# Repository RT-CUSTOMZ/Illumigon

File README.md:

# 💡 Illumigon

Die modularen smarten Leuchtpanels mit Wifi-Konnektivität, die Ihr auf der Campuswoche bauen könnt.

---

## 📦 Features

- [x] Individuell adressierbare LEDs (WS2811)
- [x] WLAN-fähige Steuerung via ESP32
- [x] Konfigurierbare Animationen und Farbpaletten
- [x] Open Source Hardware + Software (WLED)
- [x] Home Assistant Integration
- [x] Modular steckbar
- [x] Keine Kabelsalat

---

## 📁 Dateiübersicht

| Pfad / Datei                | Beschreibung                           |
|----------------------------|-----------------------------------------|
| `Fusion 360/`              | Fusion 360 Archiv und STEP-Modell       |
| `Gerber/`                  | Leiterplattenlayouts im Gerber Format   |
| `KiCad/`                   | Leiterplattenlayouts im KiCad 9 Format  |
| `STLs/`                    | 3D-Modell im STL-Format für den 3D-Druck|
| `SVGs/`                    | Vectorgrafiken zum Laserschneiden und Gravieren      |

## 🧾 Stückliste / Teilebestellung

### 🧠 ESP32 WLED Controller

| Bauteil                 | Referenz                    | Wert                        | Footprint             | Menge | Link  |
|-------------------------|-----------------------------|-----------------------------|-----------------------|-------|-------|
| Keramikkondensator      | C3, C4, C5, C7, C8, C9, C10 | 100n                        | SMD 1206              | 7     |       |
| Keramikkondensator      | C11, C12                    | 22u                         | SMD 1206              | 2     |       |
| Elektrolytkondensator   | C1                          | 470u                        | C_Elec_10x10.2        | 1     |       |
| Keramikkondensator      | C2                          | 1u0                         | SMD 1206              | 1     |       |
| Keramikkondensator      | C6                          | 10u                         | SMD 1206              | 1     |       |
| Dichschichtwiderstand   | R3, R6, R9                  | 100R                        | SMD 0805              | 3     |       |
| Dichschichtwiderstand   | R8, R11, R12                | 10K                         | SMD 1206              | 3     |       |
| Dichschichtwiderstand   | R4, R5                      | 5K1                         | SMD 1206              | 2     |       |
| Dichschichtwiderstand   | R7, R10                     | 4K7                         | SMD 0805              | 2     |       |
| Dichschichtwiderstand   | R1                          | 2K0                         | SMD 0805              | 1     |       |
| Dichschichtwiderstand   | R2                          | 470R                        | SMD 0805              | 1     |       |
| Leistungsinduktor       | L1                          | 4u7                         | 7.3x6.6mm             | 1     |       |
| Leuchtdiode             | D1, D2, D3, D5, D6          | LED                         | SMD 0805              | 5     |       |
| Schottky-Diode          | D4, D7                      | SS34                        | SMA                   | 2     |       |
| 3.3V Spannungswandler   | U1                          | AMS1117-3.3                 | SOT-223-3             | 1     |       |
| 32-bit Mikrocontroller  | U2                          | ESP32-WROOM-32E             |                       | 1     |       |
| 5V Synchr.-Schaltregler | U3                          | AP63205WU                   | TSOT-23-6             | 1     |       |
| 420Mbps Levelshifter    | U4                          | SN74LVC1T45DBV              | SOT-23-6              | 1     |       |
| USB-UART Transceiver    | U5                          | CH340C                      | SOIC-16               | 1     |       |
| Bipolartransistor       | Q2, Q3                      | BC857                       | SOT-23                | 2     |       |
| Bipolartransistor       | Q4, Q5                      | MMBT3904                    | SOT-23                | 2     |       |
| P-Kanal MOSFET          | Q1                          | Q_PMOS_GDS                  | TO-252-2              | 1     |       |
| USB-C-Buchse 16-Pin     | J1                          | USB_C_Receptacle_USB2.0_16P | GCT USB4105           | 1     |       |
| Hohlsteckerbuchse       | J2                          | Barrel_Jack_Switch          |                       | 1     |       |
| Pinheader 2.54 2x3      | J3                          | Conn_02x03_Odd_Even         | 2x03 P2.54mm Vertical | 1     |       |

### 💡 Komponenten je Panel

| Bauteil        | Referenz    | Wert       | Footprint                | Menge | Link |
|----------------|-------------|------------|--------------------------|--------|------|
| Platine        | Ecke        |            |                          | 3      | [GitHub](https://github.com/RT-CUSTOMZ/Illumigon/blob/V4/Gerber/Ecke.zip) |
| Platine        | Seite       |            |                          | 3      | [GitHub](https://github.com/RT-CUSTOMZ/Illumigon/blob/V4/Gerber/Seite.zip) |
| Plexiglas      | Lichtleiter | 4mm klar   | Acrylglas GS             | 1      | [GitHub](https://github.com/RT-CUSTOMZ/Illumigon/blob/e6f71768b751d2ca16ff6e7ad1a84dd5374f7dc3/SVGs/Light_Guide_Panel_fein.svg) |
| Plexiglas      | Diffusor    | 3mm opal   | Acrylglas XT opal 70105  | 1      | [GitHub](https://github.com/RT-CUSTOMZ/Illumigon/blob/e6f71768b751d2ca16ff6e7ad1a84dd5374f7dc3/SVGs/Diffusor.svg) |
| Pinheader 2x3  | J1          | 02x03      | Vertikal                 | 3      | [LCSC](https://www.lcsc.com/product-detail/C492420.html) |
| Pinheader 1x5  | J2, J3      | 01x05      | Horizontal               | 6      | [LCSC](https://www.lcsc.com/product-detail/C492413.html) |
| Platine        | Verbinder   |            |                          | 1      | [GitHub](https://github.com/RT-CUSTOMZ/Illumigon/blob/V4/Gerber/Verbinder.zip) |
| Pinsocket 2x3  | J1, J2      | 02x03      | Vertikal                 | 2      | [LCSC](https://www.lcsc.com/product-detail/C5116527.html) |
| Pinheader 1x2  | J3, J4      | 01x02      | Vertikal                 | 2      | [LCSC](https://www.lcsc.com/product-detail/C492401.html) |
| Jumper 1x2     |             | 01x02      |                          | 1      | [LCSC](https://www.lcsc.com/product-detail/C100114.html) |
| Schraube       |             | PZ 3x10    |                          | 3      | [Schraubenhimmel](https://www.schraubenhimmel.de/schrauben/senkkopf/spanplattenschrauben-kreuzschlitz/65940/spax-wirox-senkkopf-kreuzschlitz-pz-1-3x10-mm-vollgewinde) |
| 3D-Druck       |             | Deckel u.  |                          | 3      | [GitHub](https://github.com/RT-CUSTOMZ/Illumigon/blob/V4/STLs/Deckel_unten%20v49.stl) |
| 3D-Druck       |             | Deckel m.  |                          | 3      | [GitHub](https://github.com/RT-CUSTOMZ/Illumigon/blob/V4/STLs/Deckel_mitte%20v45.stl) |
| 3D-Druck       |             | Verbinder  |                          | 2      | [GitHub](https://github.com/RT-CUSTOMZ/Illumigon/blob/V4/STLs/Verbinder%20v9.stl) |

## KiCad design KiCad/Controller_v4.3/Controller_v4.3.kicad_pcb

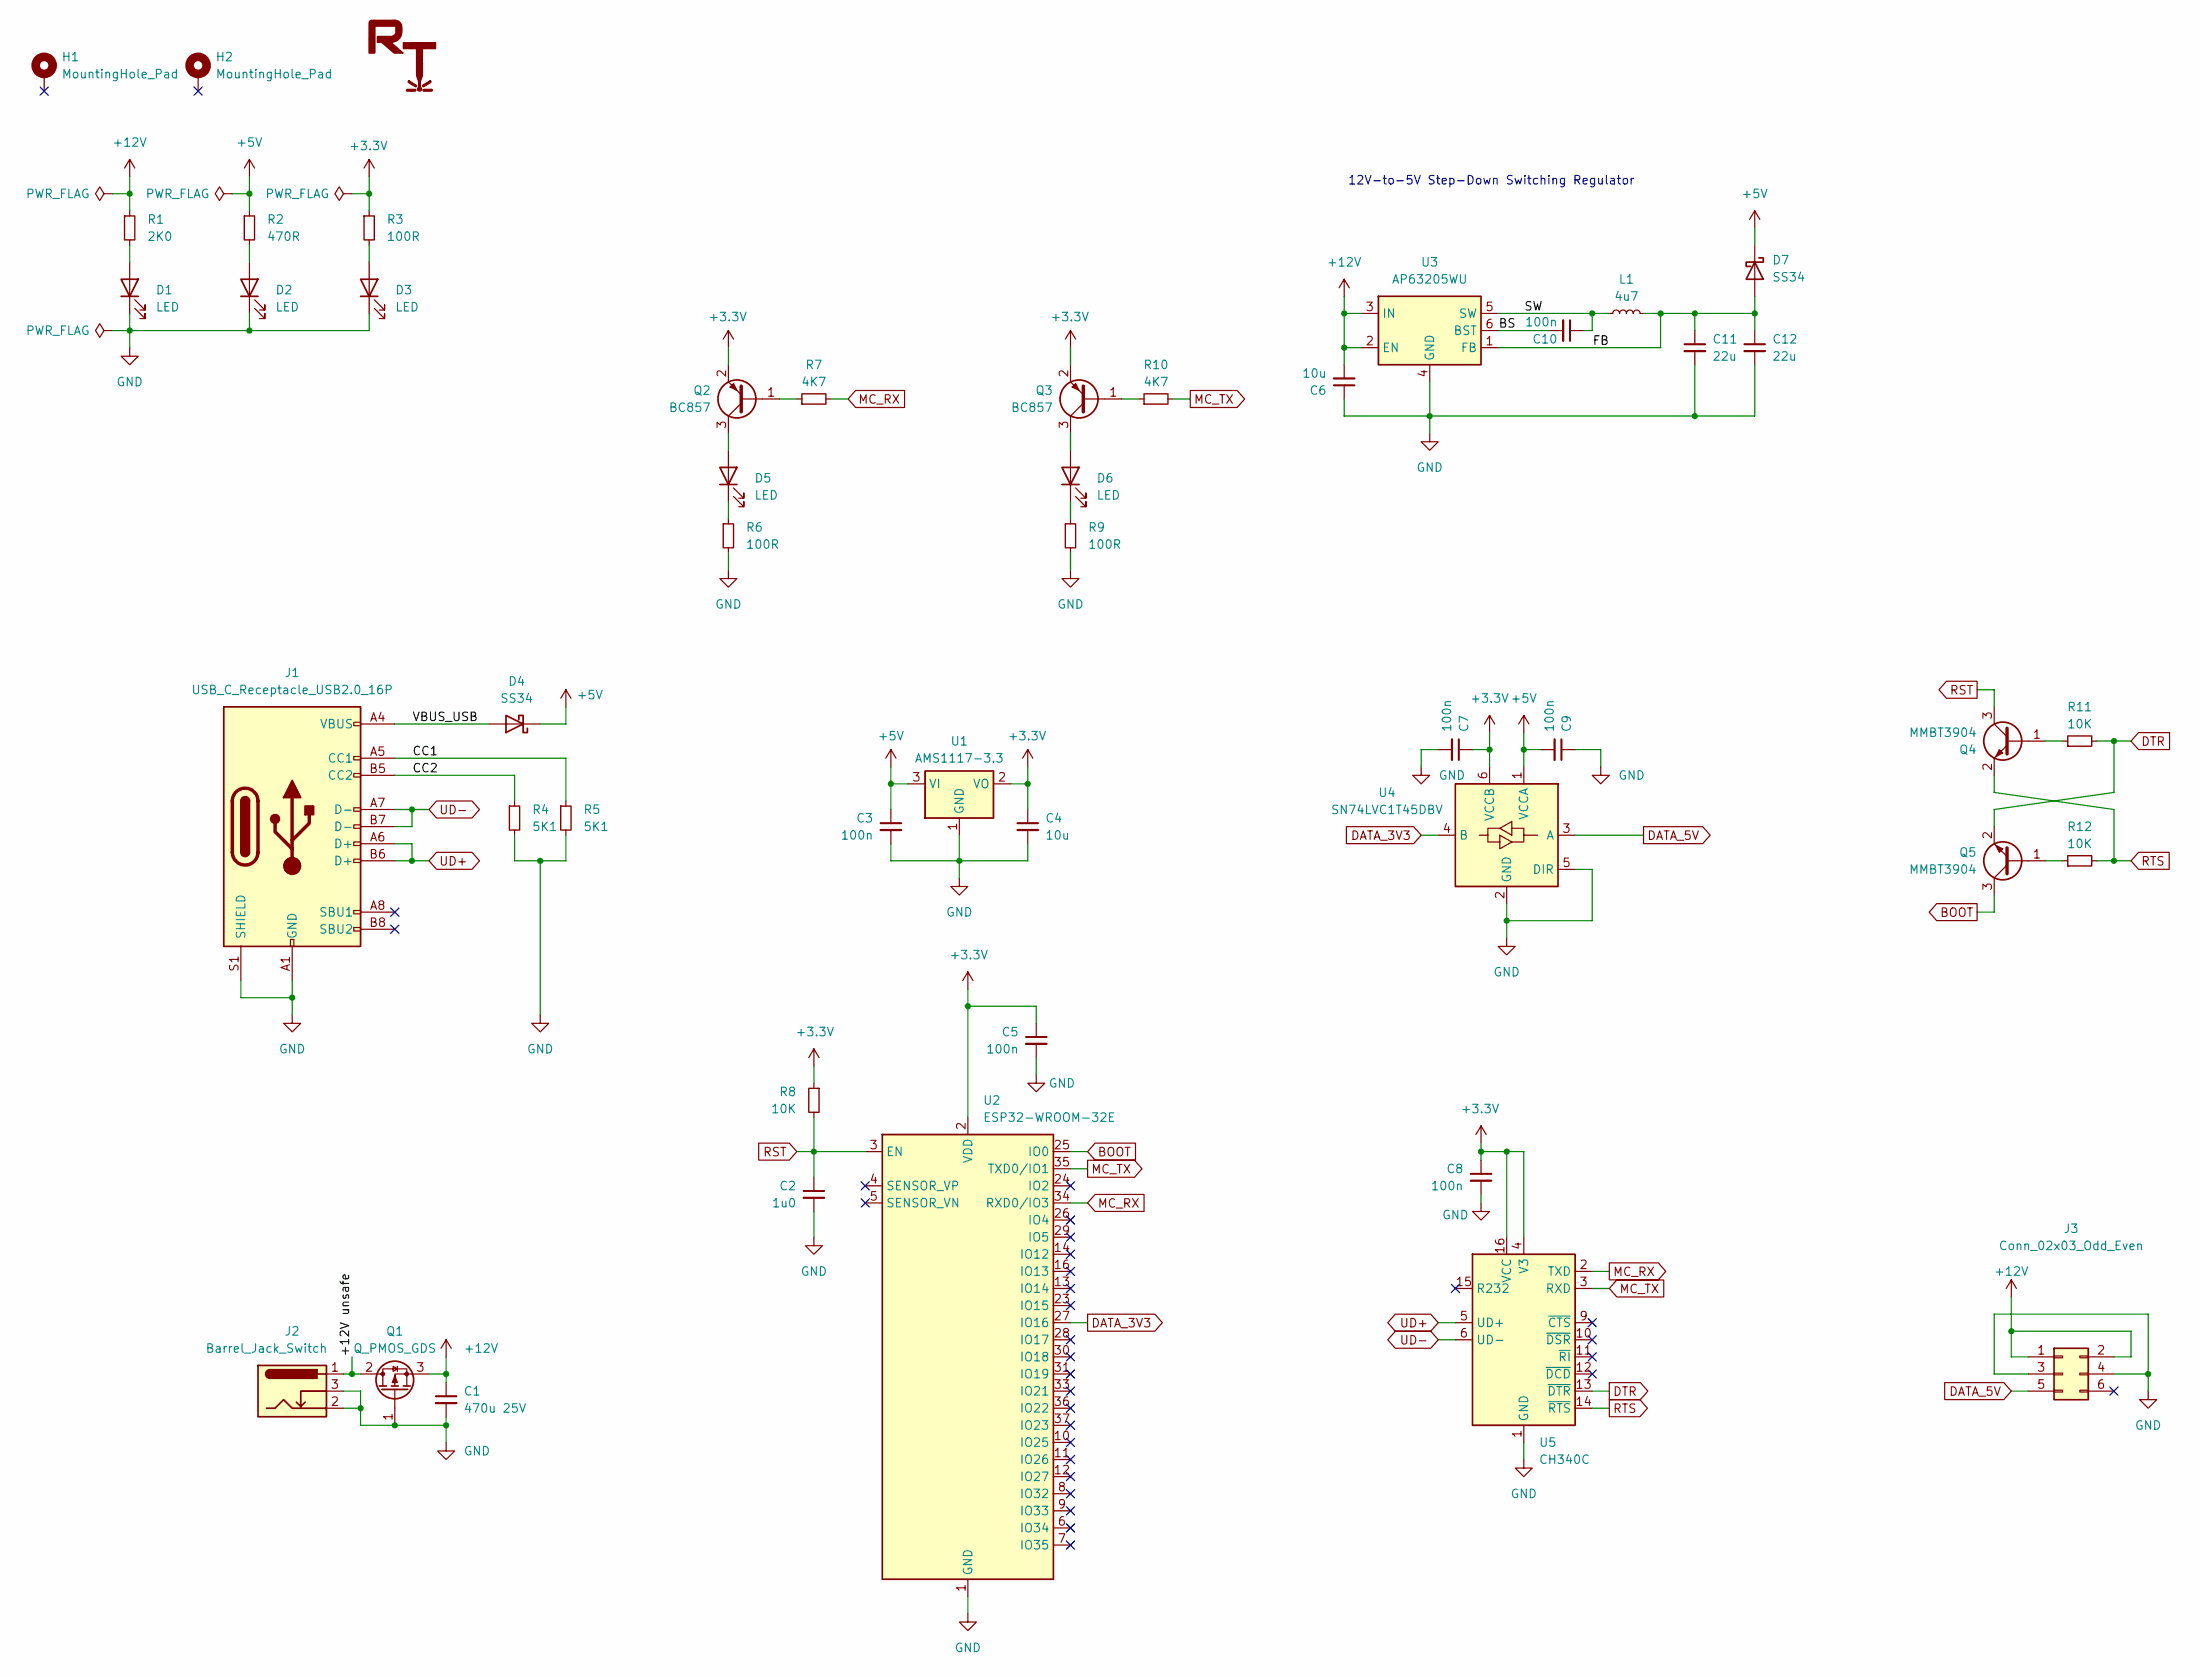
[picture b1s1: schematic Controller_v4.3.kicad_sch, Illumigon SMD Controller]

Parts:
C1: 470u 25V; C_Elec_10x10.2; Part Number EEE-FK1E471AP
C2: 1u0; C_1206_3216Metric_Pad1.33x1.80mm_HandSolder
C3, C5, C7, C8, C9, C10: 100n; C_1206_3216Metric_Pad1.33x1.80mm_HandSolder
C4, C6: 10u; C_1206_3216Metric_Pad1.33x1.80mm_HandSolder; Part Number CL31B106KAHNNNE
C11, C12: 22u; C_1206_3216Metric_Pad1.33x1.80mm_HandSolder; Part Number CL31B226MPHNNNE
D1, D2, D3, D5, D6: LED; LED_0805_2012Metric_Pad1.15x1.40mm_HandSolder
D4, D7: SS34; D_SMA
H1, H2: MountingHole_Pad; MountingHole_3.2mm_M3_DIN965_Pad_TopBottom
J1: USB_C_Receptacle_USB2.0_16P; USB_C_Receptacle_GCT_USB4105-xx-A_16P_TopMnt_Horizontal; Part Number USB4105-GF-A-120
J2: Barrel_Jack_Switch; BarrelJack_Horizontal
J3: Conn_02x03_Odd_Even; PinHeader_2x03_P2.54mm_Vertical
L1: 4u7; L_Chilisin_BMRB00060624
Q1: Q_PMOS_GDS; TO-252-2
Q2, Q3: BC857; SOT-23
Q4, Q5: MMBT3904; SOT-23
R1: 2K0; R_0805_2012Metric_Pad1.20x1.40mm_HandSolder
R2: 470R; R_0805_2012Metric_Pad1.20x1.40mm_HandSolder
R3, R6, R9: 100R; R_0805_2012Metric_Pad1.20x1.40mm_HandSolder
R4, R5: 5K1; R_1206_3216Metric_Pad1.30x1.75mm_HandSolder
R7, R10: 4K7; R_0805_2012Metric_Pad1.20x1.40mm_HandSolder
R8, R11, R12: 10K; R_1206_3216Metric_Pad1.30x1.75mm_HandSolder
SYM1: RT_Logo_10mm_Silkscreen
U1: AMS1117-3.3; SOT-223-3_TabPin2
U2: ESP32-WROOM-32E; ESP32-WROOM-32D
U3: AP63205WU; TSOT-23-6
U4: SN74LVC1T45DBV; SOT-23-6
U5: CH340C; SOIC-16_3.9x9.9mm_P1.27mm

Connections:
+3.3V: C4.1, C5.1, C7.1, C8.1, Q2.2 (E), Q3.2 (E), R3.1, R8.1, U1.2 (VO), U2.2 (VDD), U4.6 (VCCB), U5.4 (V3), U5.16 (VCC)
+5V: C3.1, C9.2, D4.1 (K), D7.1 (K), R2.1, U1.3 (VI), U4.1 (VCCA)
+12V: C1.1, C6.2, J3.1, J3.2, Q1.3 (S), R1.1, U3.2 (EN), U3.3 (IN)
/+12V unsafe: J2.1, Q1.2 (D)
/BS: C10.2, U3.6 (BST)
/CC1: J1.A5 (CC1), R5.1
/CC2: J1.B5 (CC2), R4.1
/FB: C11.1, C12.1, D7.2 (A), L1.2, U3.1 (FB)
/SW: C10.1, L1.1, U3.5 (SW)
/VBUS_USB: D4.2 (A), J1.A4 (VBUS), J1.A9 (VBUS), J1.B4 (VBUS), J1.B9 (VBUS)
BOOT: Q5.3 (C), U2.25 (IO0)
DATA_3V3: U2.27 (IO16), U4.4 (B)
DATA_5V: J3.5, U4.3 (A)
DTR: Q5.2 (E), R11.2, U5.13 (~DTR)
GND: C1.2, C2.2, C3.2, C4.2, C5.2, C6.1, C7.2, C8.2, C9.1, C11.2, C12.2, D1.1 (K), D2.1 (K), D3.1 (K), J1.A1 (GND), J1.A12 (GND), J1.B1 (GND), J1.B12 (GND), J1.S1 (SHIELD), J2.2, J2.3, J3.3, J3.4, Q1.1 (G), R4.2, R5.2, R6.2, R9.2, U1.1 (GND), U2.1 (GND), U2.15 (GND), U2.38 (GND), U2.39 (GND), U3.4 (GND), U4.2 (GND), U4.5 (DIR), U5.1 (GND)
MC_RX: R7.2, U2.34 (RXD0/IO3), U5.2 (TXD)
MC_TX: R10.2, U2.35 (TXD0/IO1), U5.3 (RXD)
unnamed: D1.2 (A), R1.2
unnamed: D2.2 (A), R2.2
unnamed: D3.2 (A), R3.2
unnamed: D5.2 (A), Q2.3 (C)
unnamed: D5.1 (K), R6.1
unnamed: D6.2 (A), Q3.3 (C)
unnamed: D6.1 (K), R9.1
unnamed: Q2.1 (B), R7.1
unnamed: Q3.1 (B), R10.1
unnamed: Q4.1 (B), R11.1
unnamed: Q5.1 (B), R12.1
RST: C2.1, Q4.3 (C), R8.2, U2.3 (EN)
RTS: Q4.2 (E), R12.2, U5.14 (~RTS)
UD+: J1.A6 (D+), J1.B6 (D+), U5.5 (UD+)
UD-: J1.A7 (D-), J1.B7 (D-), U5.6 (UD-)

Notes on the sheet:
12V-to-5V Step-Down Switching Regulator

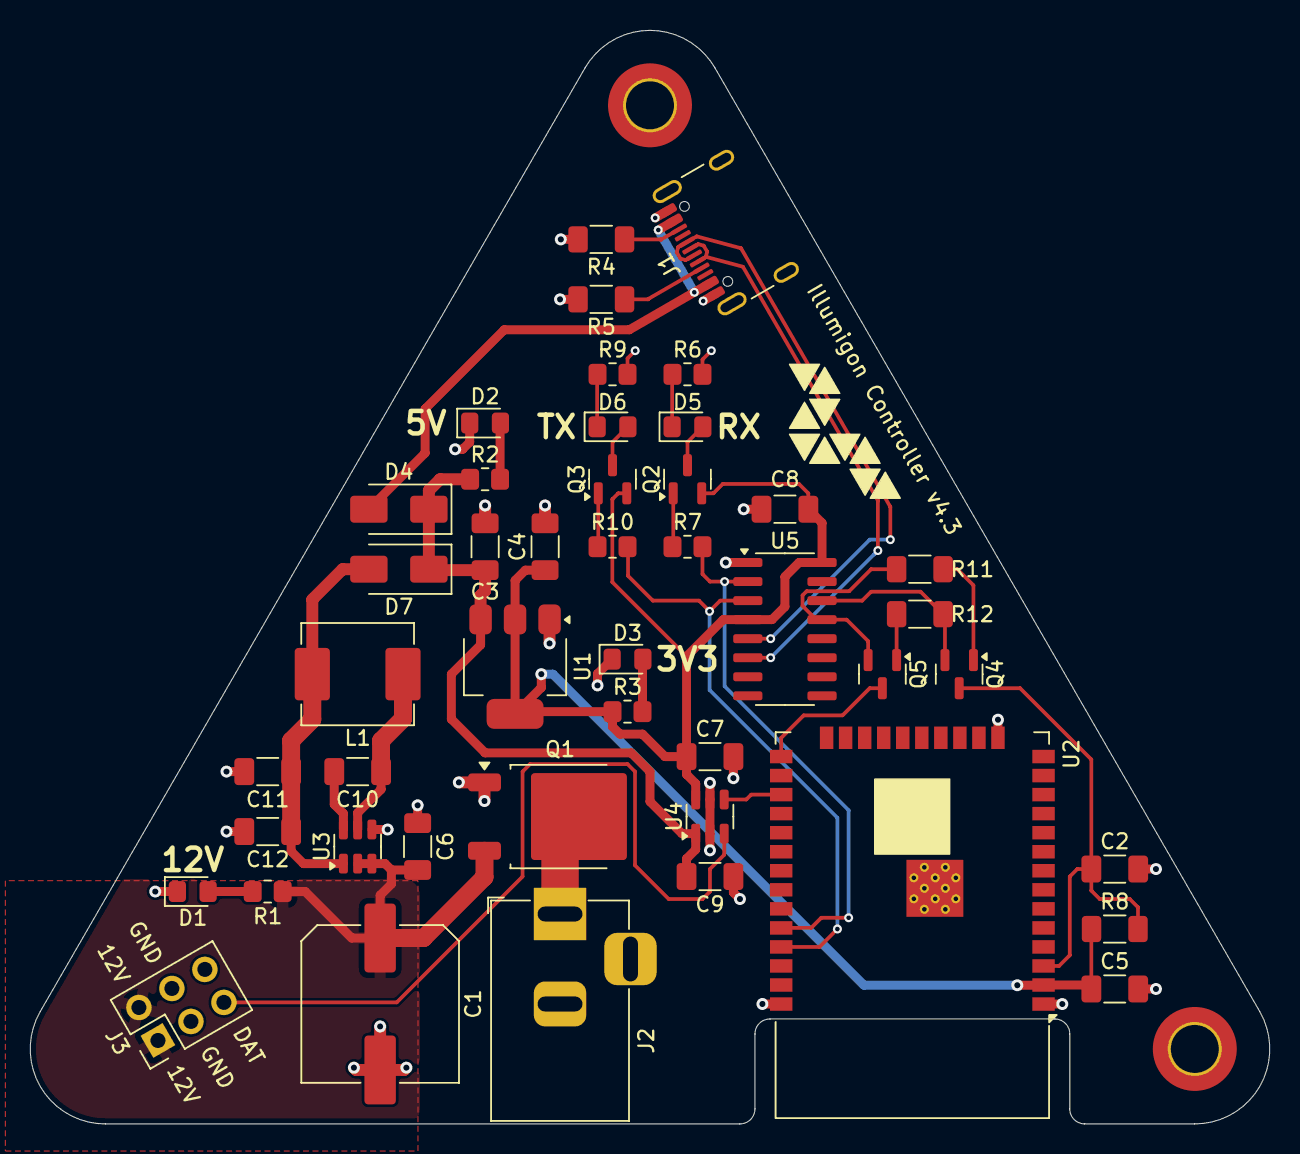
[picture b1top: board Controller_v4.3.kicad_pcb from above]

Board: 2 copper layers, 82.7 x 72.9 mm, 48 parts (1 on the bottom side), 32 nets.

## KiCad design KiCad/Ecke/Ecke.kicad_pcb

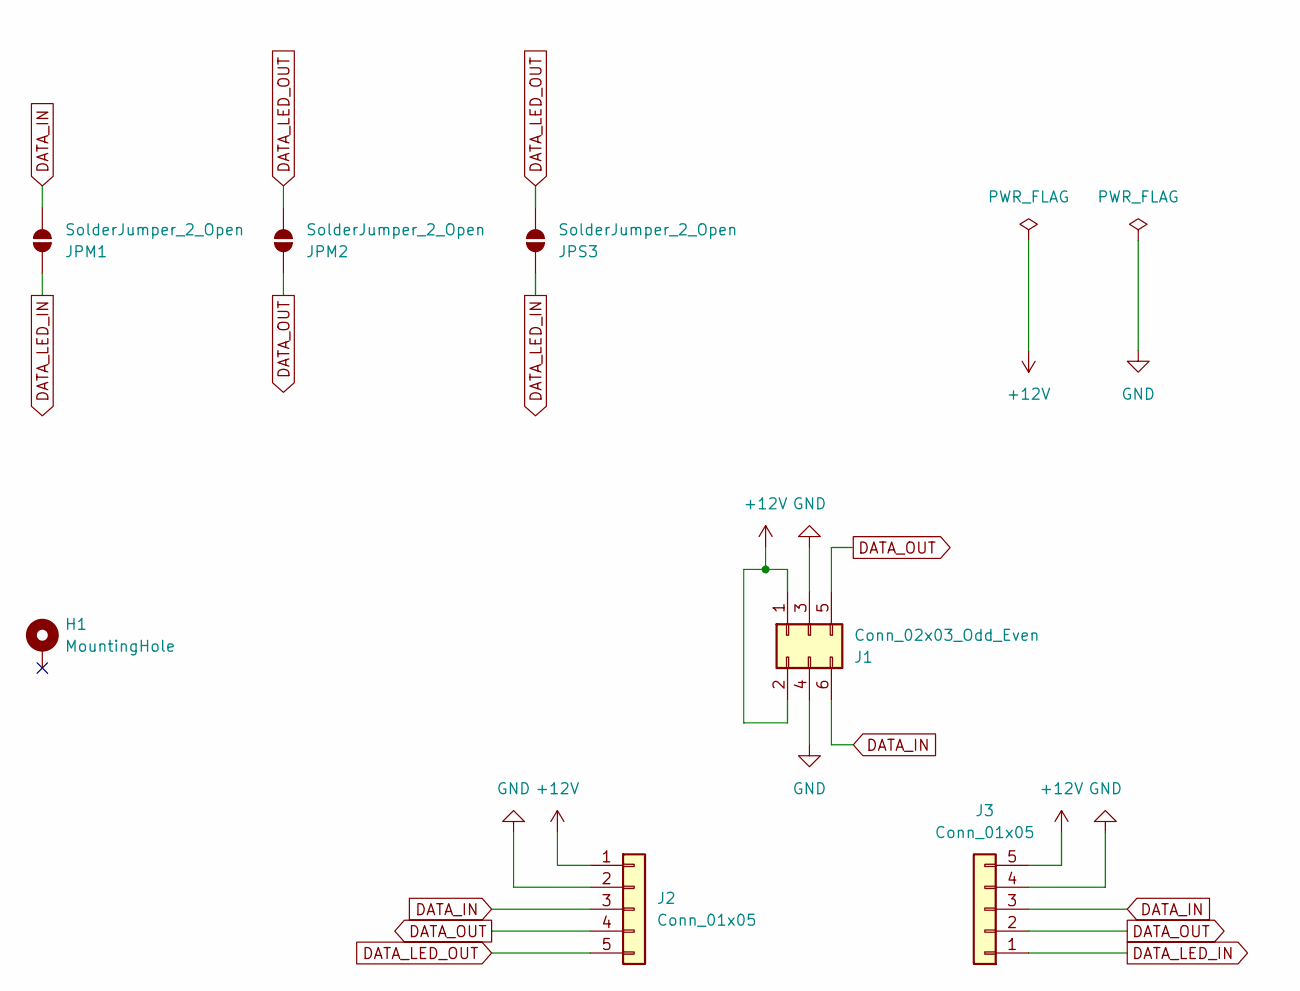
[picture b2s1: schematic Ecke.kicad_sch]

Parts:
H1: MountingHole; MountingHole_3.2mm_M3
J1: Conn_02x03_Odd_Even; PinHeader_2x03_P2.54mm_Vertical
J2, J3: Conn_01x05; PinHeader_1x05_P2.54mm_Horizontal_short_Silk
JPM1, JPM2: SolderJumper_2_Open; SolderJumper-2_P1.3mm_Open_RoundedPad1.0x1.5mm
JPS3: SolderJumper_2_Open; SolderJumper-2_P1.3mm_Open_RoundedPad1.0x1.5mm

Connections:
+12V: J1.1, J1.2, J2.1, J3.5
DATA_IN: J1.6, J2.3, J3.3, JPM1.1 (A)
DATA_LED_IN: J3.1, JPM1.2 (B), JPS3.2 (B)
DATA_LED_OUT: J2.5, JPM2.1 (A), JPS3.1 (A)
DATA_OUT: J1.5, J2.4, J3.2, JPM2.2 (B)
GND: J1.3, J1.4, J2.2, J3.4

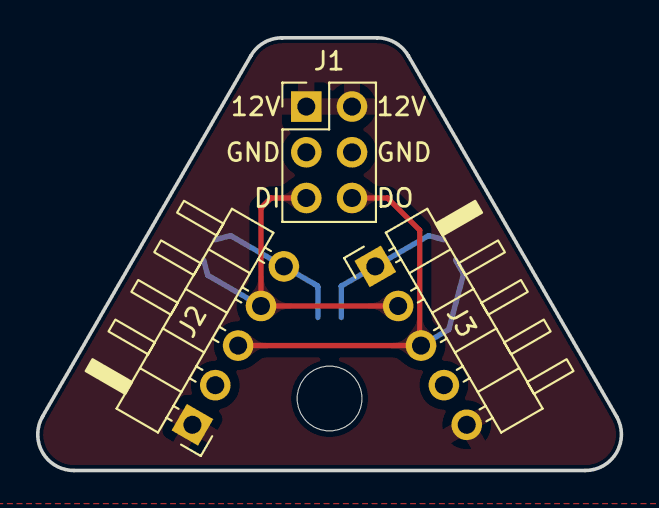
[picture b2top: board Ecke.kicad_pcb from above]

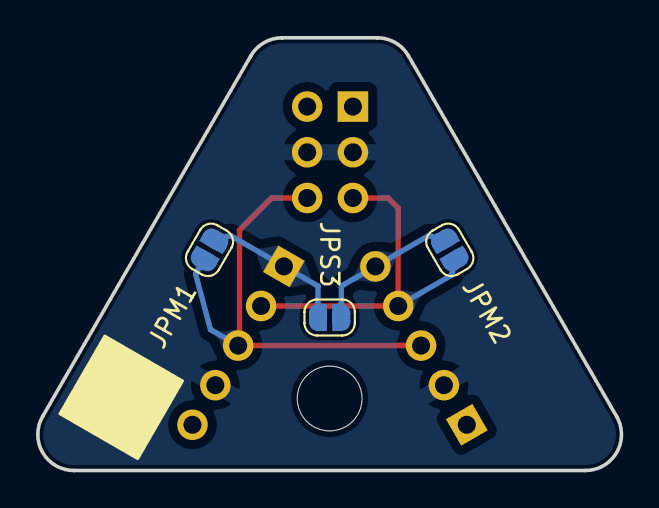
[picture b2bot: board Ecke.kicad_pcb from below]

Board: 2 copper layers, 32.4 x 24.0 mm, 7 parts (3 on the bottom side), 6 nets.

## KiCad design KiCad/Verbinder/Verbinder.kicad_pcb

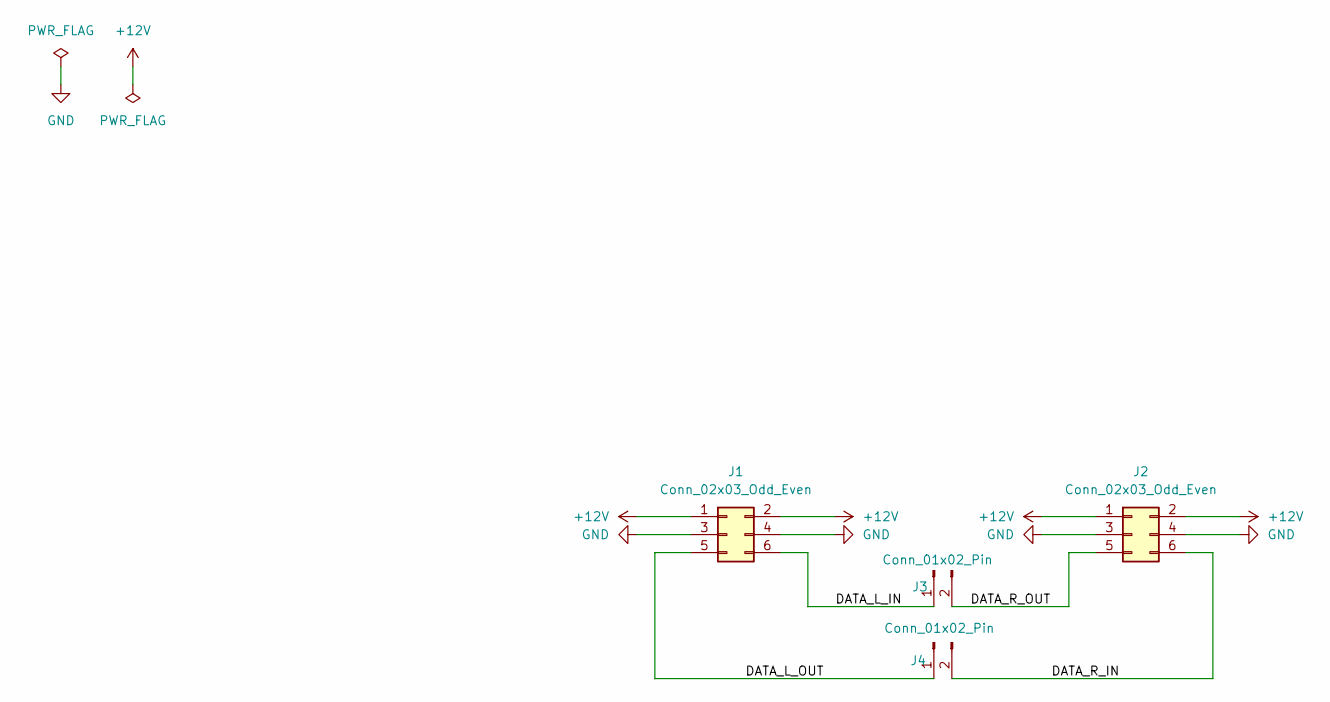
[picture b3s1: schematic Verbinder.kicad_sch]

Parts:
J1, J2: Conn_02x03_Odd_Even; PinSocket_2x03_P2.54mm_Vertical
J3, J4: Conn_01x02_Pin; PinHeader_1x02_P2.54mm_Vertical

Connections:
+12V: J1.1, J1.2, J2.1, J2.2
/DATA_L_IN: J1.6, J3.1
/DATA_L_OUT: J1.5, J4.1
/DATA_R_IN: J2.6, J4.2
/DATA_R_OUT: J2.5, J3.2
GND: J1.3, J1.4, J2.3, J2.4

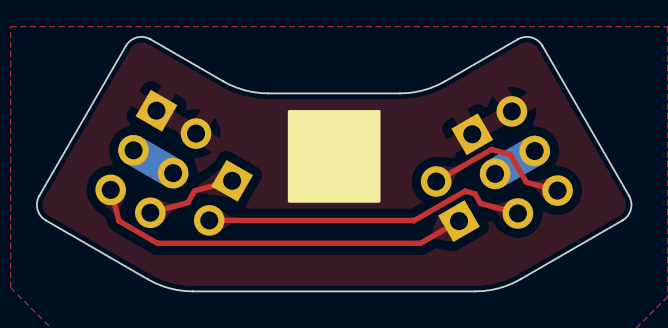
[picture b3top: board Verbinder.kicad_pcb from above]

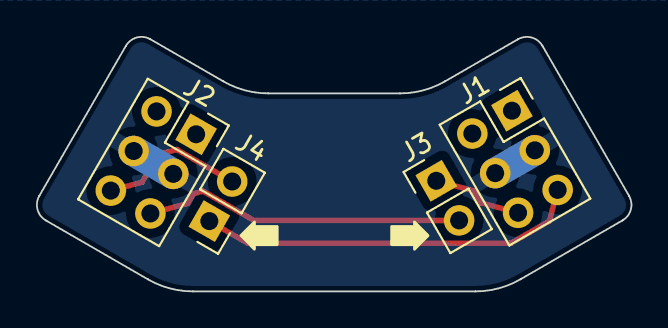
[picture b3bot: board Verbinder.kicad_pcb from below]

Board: 2 copper layers, 33.0 x 14.1 mm, 4 parts (4 on the bottom side), 6 nets.

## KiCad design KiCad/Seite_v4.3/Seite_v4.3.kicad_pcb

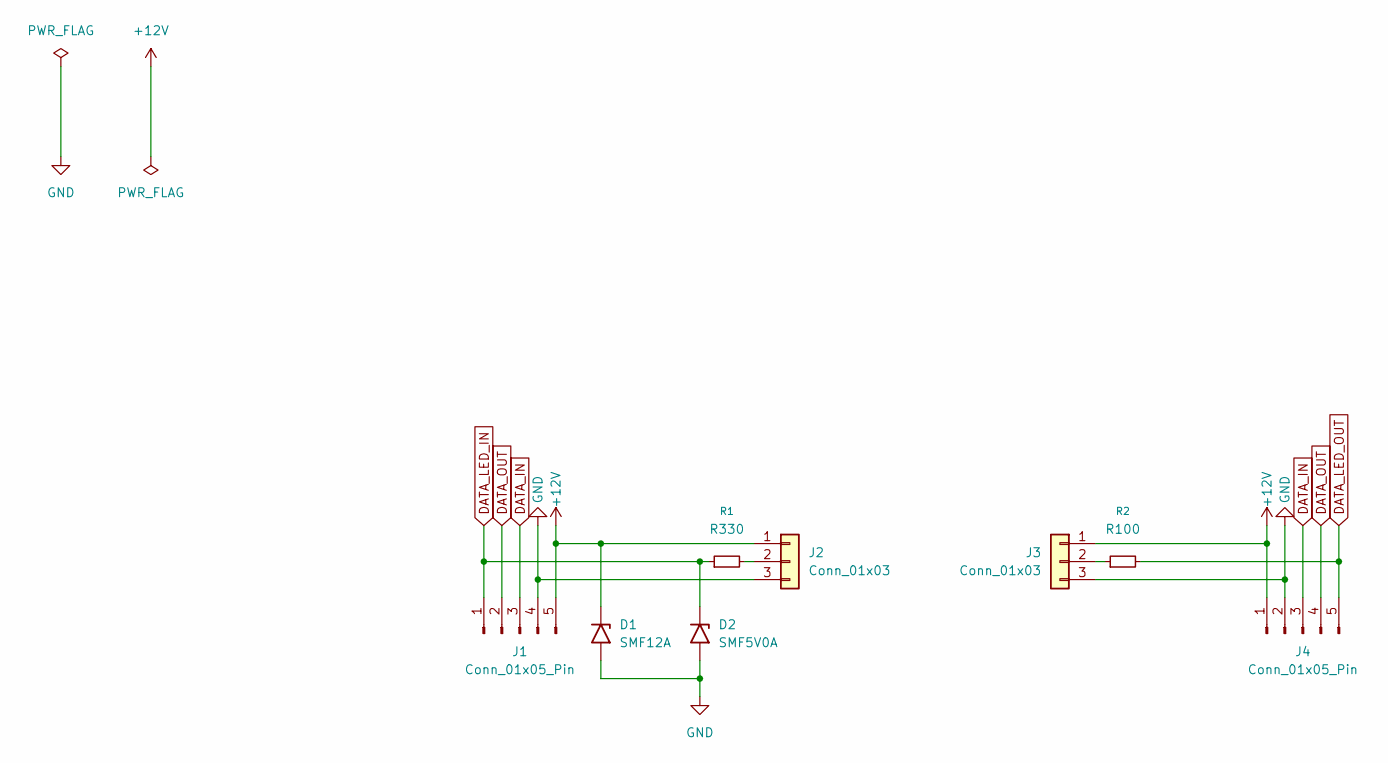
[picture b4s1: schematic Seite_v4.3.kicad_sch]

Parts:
D1: SMF12A; D_SMF
D2: SMF5V0A; D_SMF
J1, J4: Conn_01x05_Pin; PinSocket_1x05_P2.54mm_Vertical
J2: Conn_01x03; FCOB RGB LED Strip links
J3: Conn_01x03; FCOB RGB LED Strip rechts
R1: R330; R_0805_2012Metric_Pad1.20x1.40mm_HandSolder
R2: R100; R_0805_2012Metric_Pad1.20x1.40mm_HandSolder

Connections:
+12V: D1.1 (A1), J1.5, J2.1, J3.1, J4.1
DATA_IN: J1.3, J4.3
DATA_LED_IN: D2.1 (A1), J1.1, R1.1
DATA_LED_OUT: J4.5, R2.2
DATA_OUT: J1.2, J4.4
GND: D1.2 (A2), D2.2 (A2), J1.4, J2.3, J3.3, J4.2
unnamed: J2.2, R1.2
unnamed: J3.2, R2.1

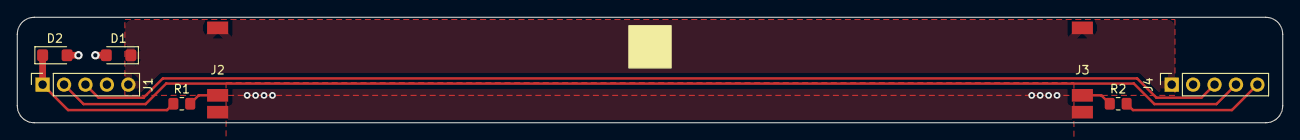
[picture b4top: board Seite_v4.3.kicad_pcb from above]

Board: 2 copper layers, 150.0 x 12.5 mm, 8 parts (0 on the bottom side), 8 nets.

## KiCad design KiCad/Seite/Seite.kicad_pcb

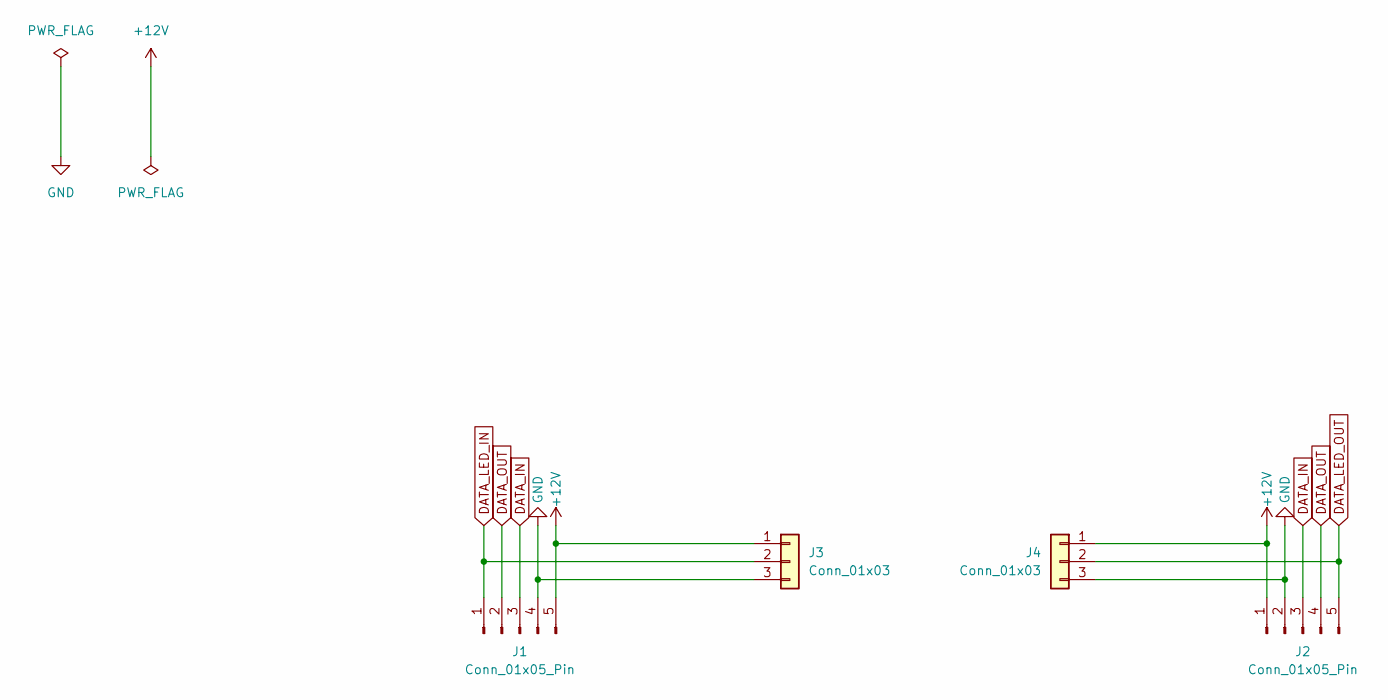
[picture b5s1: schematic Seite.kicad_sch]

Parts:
J1, J2: Conn_01x05_Pin; PinSocket_1x05_P2.54mm_Vertical
J3: Conn_01x03; FCOB RGB LED Strip links
J4: Conn_01x03; FCOB RGB LED Strip rechts

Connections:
+12V: J1.5, J2.1, J3.1, J4.1
DATA_IN: J1.3, J2.3
DATA_LED_IN: J1.1, J3.2
DATA_LED_OUT: J2.5, J4.2
DATA_OUT: J1.2, J2.4
GND: J1.4, J2.2, J3.3, J4.3

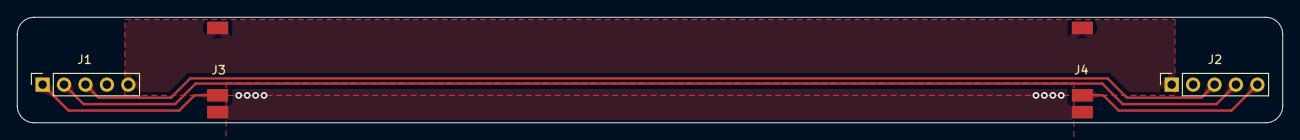
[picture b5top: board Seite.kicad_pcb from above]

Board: 2 copper layers, 150.0 x 12.5 mm, 4 parts (0 on the bottom side), 6 nets.

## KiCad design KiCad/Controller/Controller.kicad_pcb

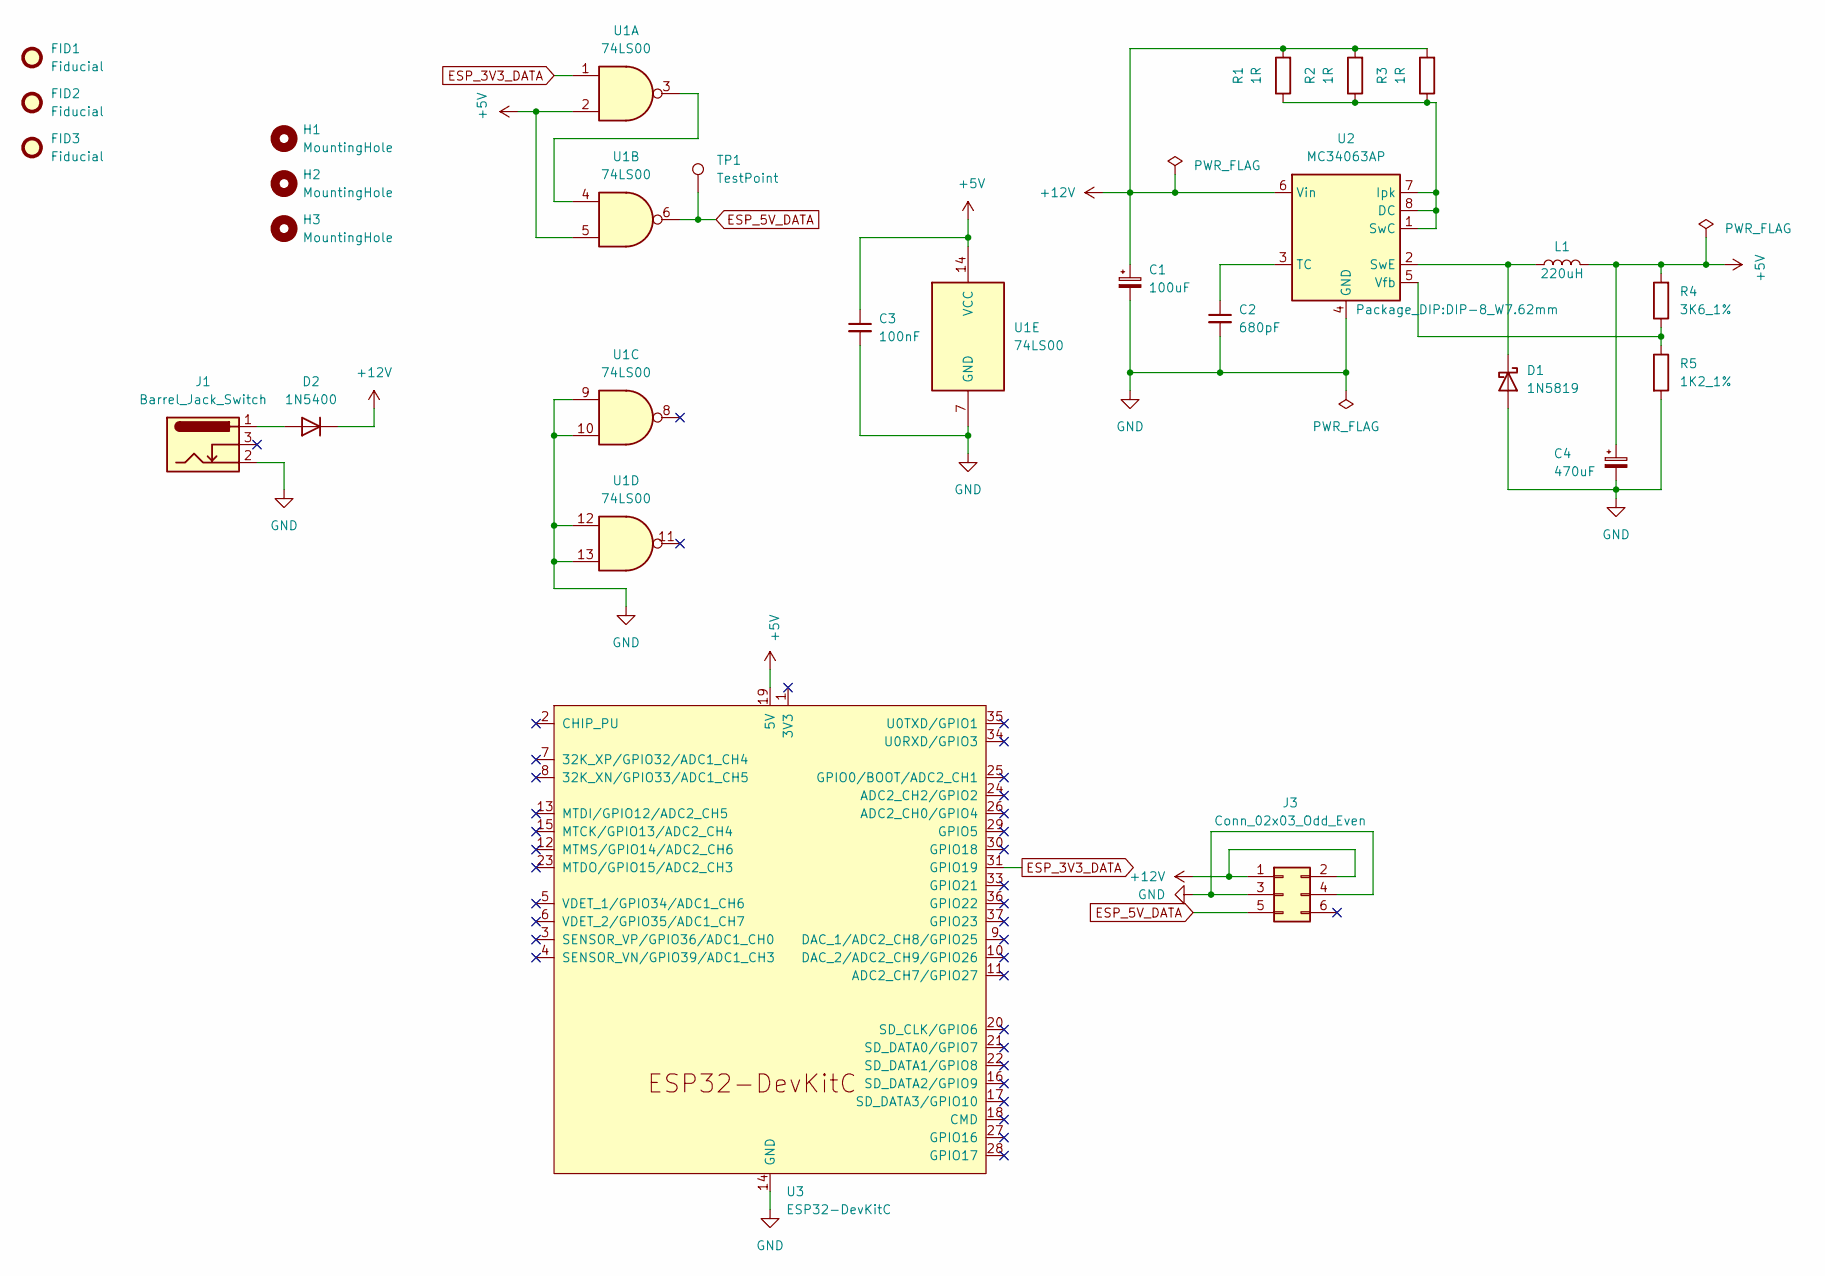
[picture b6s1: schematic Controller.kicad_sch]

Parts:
C1: 100uF; CP_Radial_D5.0mm_P2.50mm
C2: 680pF; C_Rect_L4.0mm_W2.5mm_P2.50mm
C3: 100nF; C_Rect_L7.0mm_W2.5mm_P5.00mm
C4: 470uF; CP_Radial_D10.0mm_P5.00mm
D1: 1N5819; D_DO-41_SOD81_P10.16mm_Horizontal
D2: 1N5400; D_DO-201AD_P15.24mm_Horizontal
FID1, FID2, FID3: Fiducial; Fiducial_1.5mm_Mask3mm
H1, H2, H3: MountingHole; MountingHole_2.5mm
J1: Barrel_Jack_Switch; BarrelJack_Horizontal
J3: Conn_02x03_Odd_Even; PinHeader_2x03_P2.54mm_Vertical
L1: 220uH; L_Radial_D12.5mm_P7.00mm_Fastron_09HCP
R1, R2, R3: 1R; R_Axial_DIN0207_L6.3mm_D2.5mm_P10.16mm_Horizontal
R4: 3K6_1%; R_Axial_DIN0207_L6.3mm_D2.5mm_P10.16mm_Horizontal
R5: 1K2_1%; R_Axial_DIN0207_L6.3mm_D2.5mm_P10.16mm_Horizontal
TP1: TestPoint; TestPoint_Pad_D2.0mm
U1: 74LS00; DIP-14_W7.62mm_Socket_LongPads
U2: MC34063AP; DIP-8_W7.62mm
U3: ESP32-DevKitC

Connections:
+5V: C3.1, C4.1, L1.2, R4.2, U1.2, U1.5, U1.14 (VCC), U3.19 (5V)
+12V: C1.1, D2.1 (K), J3.1, J3.2, R1.2, R2.2, R3.2, U2.6 (Vin)
ESP_3V3_DATA: U1.1, U3.31 (GPIO19)
ESP_5V_DATA: J3.5, TP1.1, U1.6
GND: C1.2, C2.2, C3.2, C4.2, D1.2 (A), J1.2, J3.3, J3.4, R5.2, U1.7 (GND), U1.9, U1.10, U1.12, U1.13, U2.4 (GND), U3.14 (GND), U3.32 (GND), U3.38 (GND)
unnamed: D1.1 (K), L1.1, U2.2 (SwE)
unnamed: D2.2 (A), J1.1
unnamed: U1.3, U1.4
unnamed: R1.1, R2.1, R3.1, U2.1 (SwC), U2.7 (Ipk), U2.8 (DC)
unnamed: C2.1, U2.3 (TC)
unnamed: R4.1, R5.1, U2.5 (Vfb)

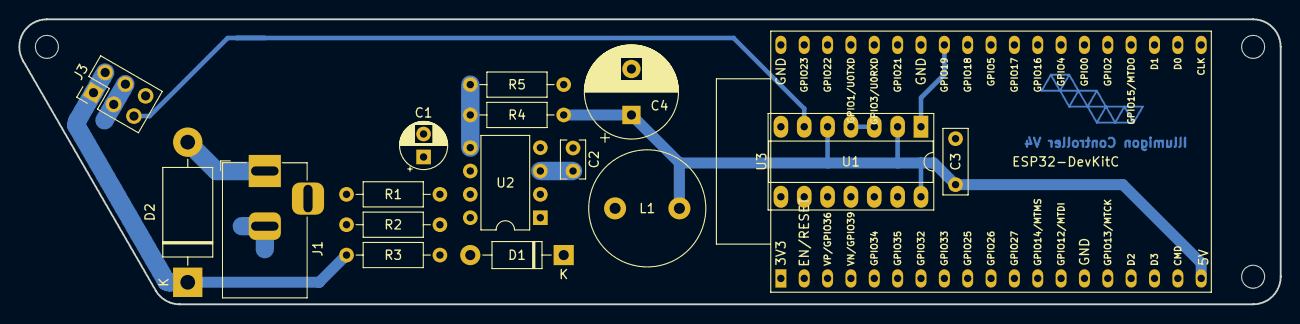
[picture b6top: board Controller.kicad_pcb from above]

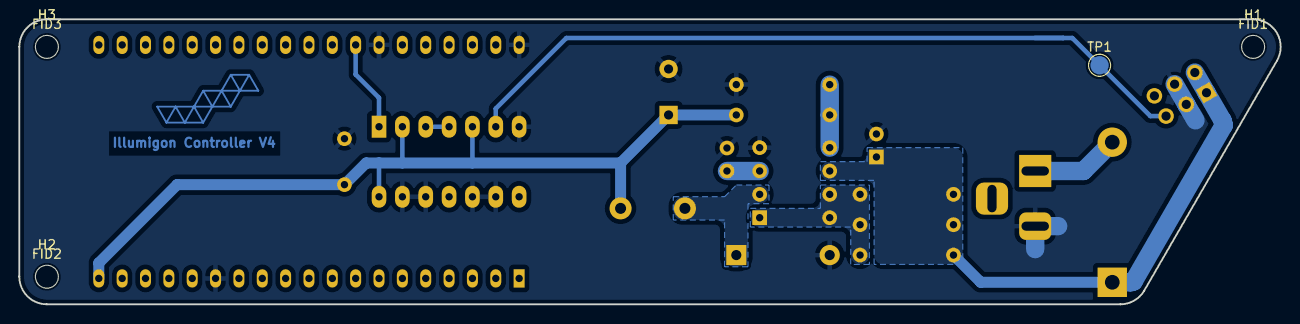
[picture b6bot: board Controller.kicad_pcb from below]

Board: 2 copper layers, 137.2 x 31.0 mm, 24 parts (7 on the bottom side), 11 nets.

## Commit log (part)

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2026-05-28 V4.3 Controller und Seite KiCad Dateien
2026-05-28 gitignore geupdatet
2026-05-28 Ecke und Verbinder hinzugefuegt
2026-05-28 Relabeled Components
